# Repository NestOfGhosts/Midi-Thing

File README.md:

# Midi-Thing
Basic midi device, also can be played live with headphones

## BOM
|Item                    |Qty|Supplier|Cost/item|Total Cost|
|Switches                |50 |[Amazon](https://www.amazon.ca/gp/product/B0GVSBNSHM?smid=&psc=1) |$0.08    |$4.00     |
|Keycaps                 |24 |[Amazon](https://www.amazon.ca/Mechkeeb-Profile-Switches-Keyboard-Replacement/dp/B0BWDTBF1L?crid=17D24DACDDXK7&dib=eyJ2IjoiMSJ9.QgzrbHYNnySbWz_C8JOt7rSGQp54UpmJIuUW7RZGzSMhlxsqRpD4ByujW6NLF5VClUPdJ7uM4nQ8F1Wo1ICEtZLIsUh5DFbeM6mQrp3peg8PTgZnUxkqFvN2t2KJmAUsvgxP33V13MaYIHIlzXmSsfT07KRJhDBgixe5str7y4PYlFrjQzKIyweJUwUIdNhgg6qZyp8ZMlW65B0i-uvvX06MY4sBke1bJfpvTXwIA8cM7RHbJqhZMl9JY1I73jYi5AkKh6-AJLnbDJc98ZBc_Pu7R-gI93cZwj5XZ4giP6E.ocRhOoAWpWF7jiiZ7ZU1jz1r0Lgcl5A6FctMVWPJO_U&dib_tag=se&keywords=10%2Bpack%2Bkeycaps&qid=1792860838&refinements=p_76%3A3276484011&rnid=3276483011&rps=1&s=electronics&sbo=RZvfv%2F%2FHxDF%2BO5021pAnSA%3D%3D&sprefix=10%2Bpack%2Bkeycaps%2Celectronics%2C151&sr=1-12&th=1) |$0.41    |$9.84     |
|Round Potentiometer     |1  |[Mouser](https://www.mouser.ca/en/ProductDetail/Alpha-Taiwan/RD901F-40-15R1-B100K-00DL1?qs=1mbolxNpo8czbLgndpJJVQ%3D%3D) |$4.53    |$4.53     |
|Long Potentiometer      |1  |[Mouser](https://www.mouser.ca/en/ProductDetail/652-PTA3432010CIB103) |$2.13    |$2.13     |
|Teensy 4.0              |1  |[Amazon](https://www.amazon.ca/gp/product/B07W5J3WNH?smid=A33HV3N1GS7LPU&psc=1)  |$27.22   |$27.22    |
|Audio shield for Teensy |1  |[Amazon](https://www.amazon.ca/gp/product/B07Z6NW913?smid=A33HV3N1GS7LPU&psc=1) |$17.37   |$17.37    |
|PCB                     |5  |[JLCPCB](https://jlcpcb.com) |$2.06    |$10.30    |
|Header Pins             |2  |[Mouser](https://www.mouser.ca/en/ProductDetail/SparkFun/PRT-13925?qs=wwacUt%252BV97tqN1BEfmG0Sg%3D%3D) |$2.31    |$4.62     |
|Estimated total shipping|1  |        |         |$42.68    |

- PCB: use [the production files](https://github.com/NestOfGhosts/Midi-Thing/blob/main/Pcb%20Production/production.zip) and a pcb printing service like [JLCPCB](https://jlcpcb.com/) to get.

- Switches and caps: use whatever as long as is cherry mx 5 pin compatible

## Assembly 

- Enter the teensy's bootloader mode by pressing the button. You can tell it works if the led turns off

- Connect the teensy onto the pcb

- Load [firmware.hex](https://github.com/NestOfGhosts/Midi-Thing/blob/main/firmware.hex) using the [Teensy Loader](https://www.pjrc.com/teensy/loader.html)

- Solder the teensy onto the shield, and the shield to the pcb (using the header pins).

Placeholder ADD IMAGE

- Solder the keys, and the pots

ADD images

- Attach the caps and stuff

Add more images

Should work now. I dunno dude rn im not done coding yet so i dunno exact process.

## Optional stuff

- Modify the code by copying [midee](https://github.com/NestOfGhosts/Midee) and recompiling with platformIO. Most things can be changed using [config.h](https://github.com/NestOfGhosts/Midee/blob/master/include/config.h)

- Print the [holder](https://github.com/NestOfGhosts/Midi-Thing/tree/main/holder)

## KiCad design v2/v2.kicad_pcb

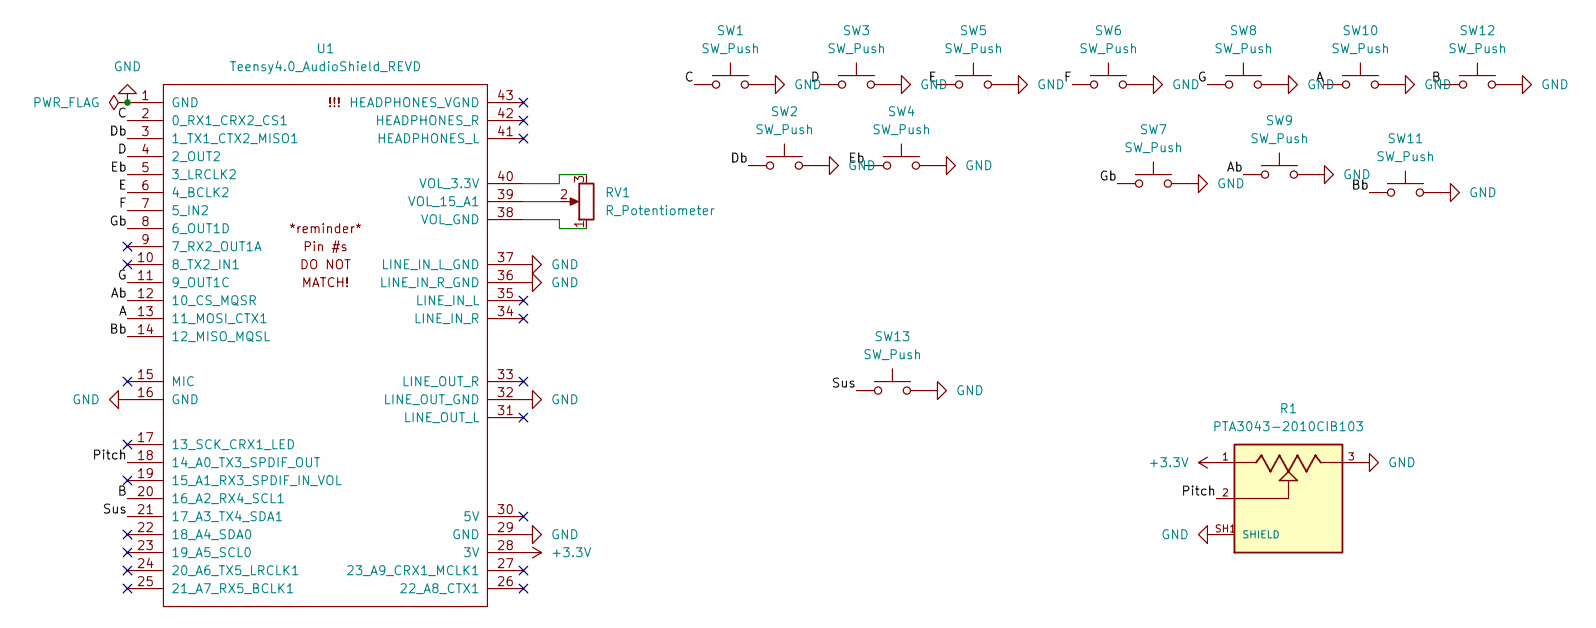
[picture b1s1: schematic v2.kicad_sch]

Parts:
R1: PTA3043-2010CIB103; TRIM_PTA3043-2010CIB103; PARTREV 04/21
RV1: R_Potentiometer; Potentiometer_Alpha_RD901F-40-00D_Single_Vertical
SW1, SW2, SW3, SW4, SW5, SW6, SW7, SW8, SW9, SW10, SW11, SW12, SW13: SW_Push; SW_Cherry_MX_1.00u_PCB
U1: Teensy4.0_AudioShield_REVD; 4.0audioshield

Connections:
+3.3V: R1.1, U1.28 (3V)
/A: SW10.1, U1.13 (11_MOSI_CTX1)
/Ab: SW9.1, U1.12 (10_CS_MQSR)
/B: SW12.1, U1.20 (16_A2_RX4_SCL1)
/Bb: SW11.1, U1.14 (12_MISO_MQSL)
/C: SW1.1, U1.2 (0_RX1_CRX2_CS1)
/D: SW3.1, U1.4 (2_OUT2)
/Db: SW2.1, U1.3 (1_TX1_CTX2_MISO1)
/E: SW5.1, U1.6 (4_BCLK2)
/Eb: SW4.1, U1.5 (3_LRCLK2)
/F: SW6.1, U1.7 (5_IN2)
/G: SW8.1, U1.11 (9_OUT1C)
/Gb: SW7.1, U1.8 (6_OUT1D)
/Pitch: R1.2, U1.18 (14_A0_TX3_SPDIF_OUT)
/Sus: SW13.1, U1.21 (17_A3_TX4_SDA1)
GND: R1.3, R1.SH1 (SHIELD), R1.SH2 (SHIELD), R1.SH3 (SHIELD), R1.SH4 (SHIELD), SW1.2, SW2.2, SW3.2, SW4.2, SW5.2, SW6.2, SW7.2, SW8.2, SW9.2, SW10.2, SW11.2, SW12.2, SW13.2, U1.1 (GND), U1.16 (GND), U1.29 (GND), U1.32 (LINE_OUT_GND), U1.36 (LINE_IN_R_GND), U1.37 (LINE_IN_L_GND)
unnamed: RV1.3, U1.40 (VOL_3.3V)
unnamed: RV1.2, U1.39 (VOL_15_A1)
unnamed: RV1.1, U1.38 (VOL_GND)

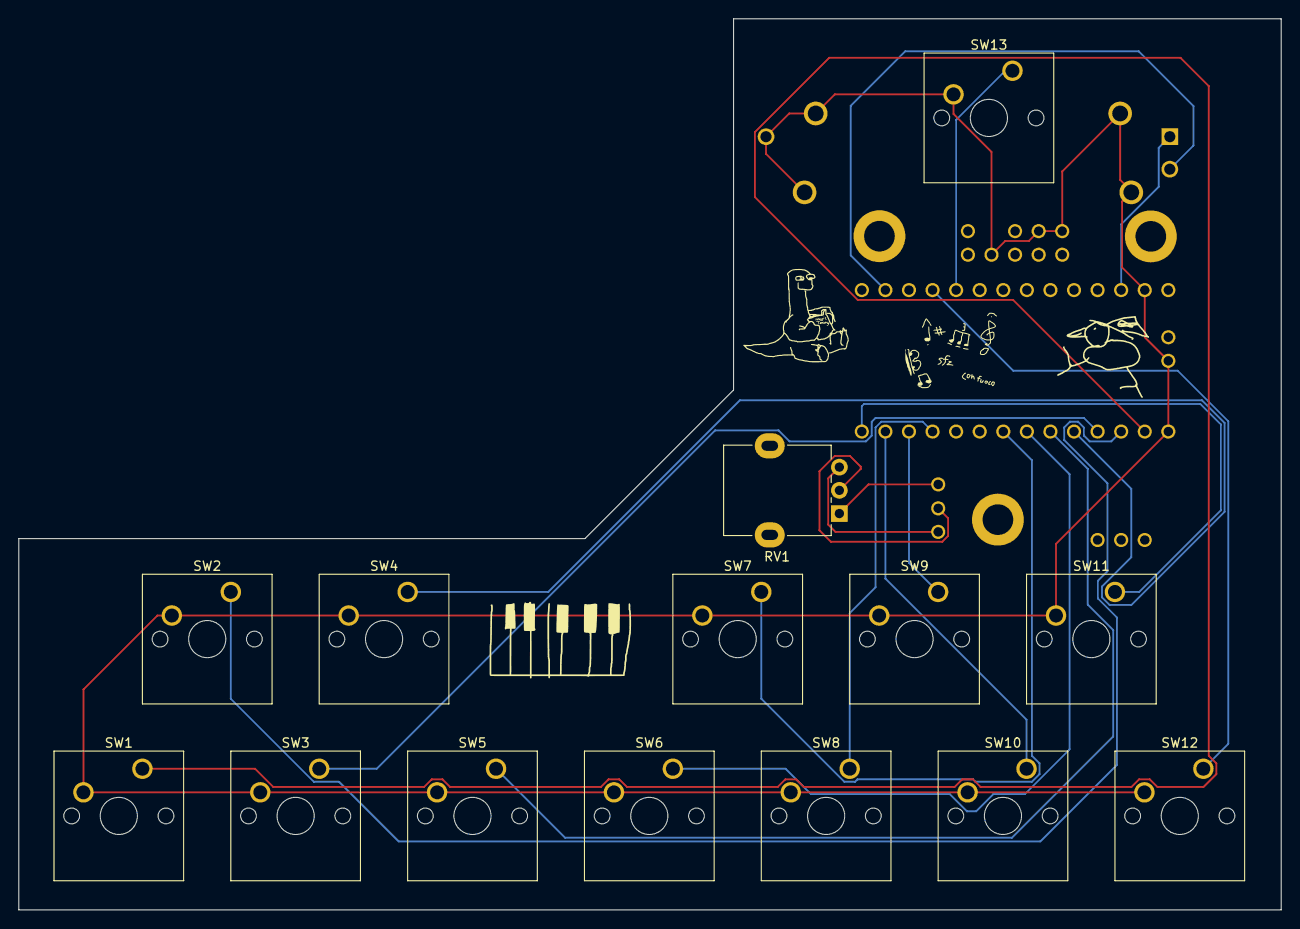
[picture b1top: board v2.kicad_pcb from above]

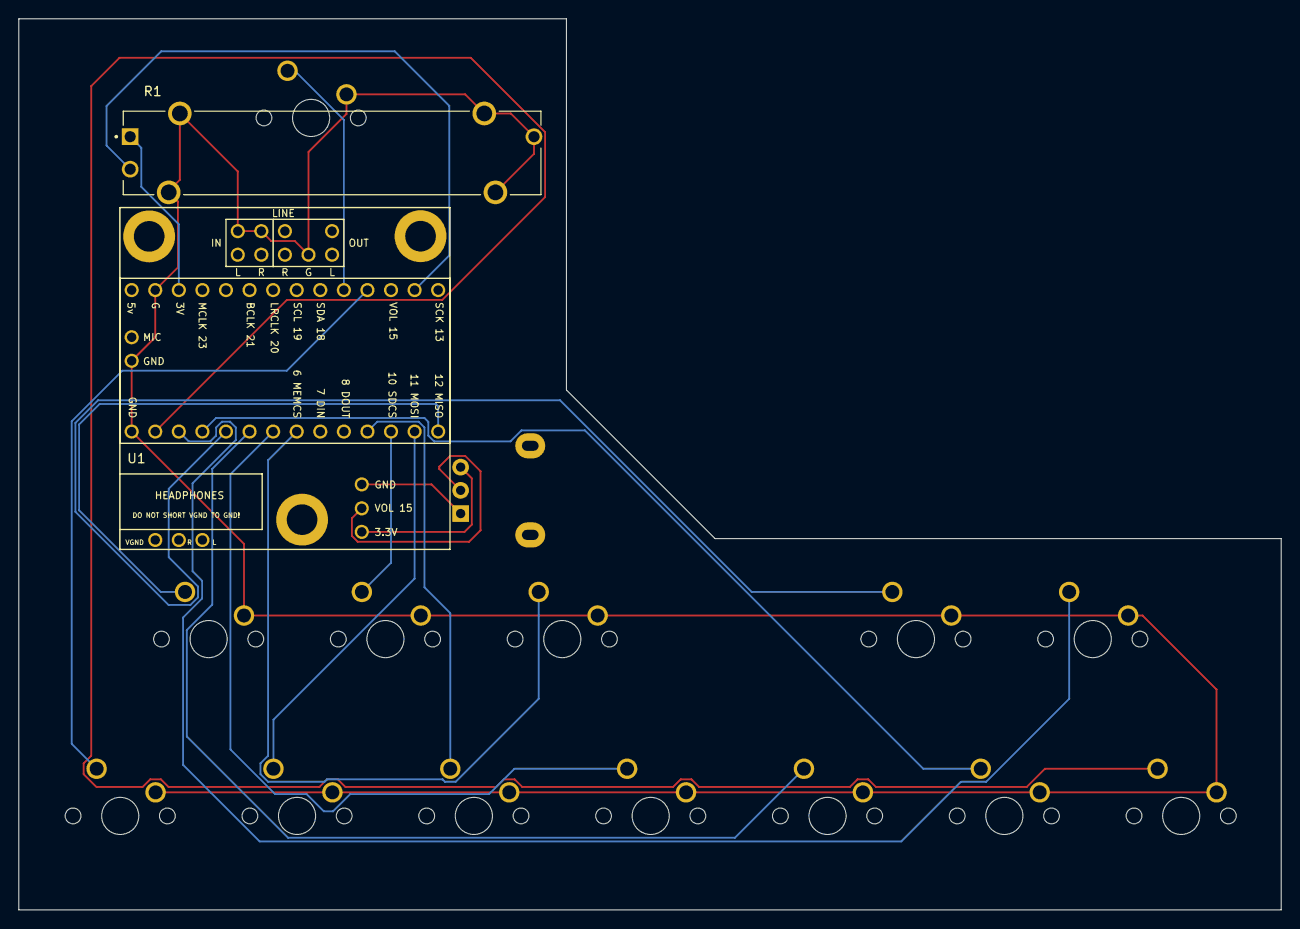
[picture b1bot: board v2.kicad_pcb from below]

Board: 2 copper layers, 136.0 x 96.0 mm, 16 parts (2 on the bottom side), 19 nets.
